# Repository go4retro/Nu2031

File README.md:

# Nu2031 

This adapter allows one to utilize a Commodore 1541 disk drive as both a serial disk drive for the serial IEC-based Commodore computers (VIC-20, C64, +4, C16, C128, etc.) and also an IEEE-488 drive for the PET/CBM line of computer systems.

## Introduction

Nu2031 ("New" 2031, with new in quotes because it's not really new :-)) comprises a two part hardware modification for the Commodore 1541 disk drive.  The first part is a 6522 Versatile Interface Adapter (VIA) daughterboard that dynamically switches specific VIA signals between the existing 1541 serial IEC port and an on-board IEEE-488 interface. The second part is a special multi-bank ROM-el replacement ROM that contains both the original 1541 DOS and a patched DOS that will enable the 1541 drive to function as a IEEE-488 CBM 2031 workalike drive. Using a single switch, connected to both adapter boards, the system can be quickly switched from one interface to the other.

This design is a refinement of many previous conversion projects, listed below:

The original (and largest, in my opinion) effort was included in an old 64'er magazine article.  Andre Fachat, who built the original interface, re-created the schematic and re-typed in the DOS patching utility, which are available at  http://www.6502.org/users/andre/cbmhw/ieee488/index.html. 

Dirk Wouters improved on the design by allowing the conversion to be "switched off", allowing continued use of the 1541 as a 1541 drive while supporting the IEEE-488 functionality.  Though his plans are no longer available, the project is discussed at https://www.lemon64.com/forum/viewtopic.php?t=71124 and at https://www.forum64.de/index.php?thread/91569-1541-to-ieee488-trimod-adapter/ (German).

Nu2031 was started before Dirk's project was presented, so it does not borrow from that design, though the two projects share a common set of functionality.

## Technical Details

The heart of the unit is the main adapter PCB (the ROM board is just a simple multi-bank ROM). The PCB contains both the 75160 and 75161 IEEE-488 interface ICs, as well as a Xilinx XC9572XL Complex Programmable Logic Device (CPLD).  Unlike the initial 64'er/Andre Fachat project, which simply wired the VIC to the interface ICs, or Dirk Wouter's interface, which uses banks of quad bilateral CMOS 4066 bilateral switches to connect or disconnect the various VIA signals to the 1541 motherboard or the IEEE 488 bus transceivers, this design implements the various IEEE-488 signal directions, as noted on page 2 of the 75161B datasheet (https://www.ti.com/lit/gpn/sn75161b). For reference, DC is always 'H' (5V), so the truth table can be somewhat simplified. The  ROM select signal noth only chooses which ROM bank to use, but is also used by the design to select which interface to enable.  The deselected interface is configured to allow other devices to continue to function on the de-selected bus.

If the system sees the ROM select signal change state, the interface immediately reconfigures the interface connects and resets the drive so the correct ROM will be initialized.

## Future Directions:

- Support method to "softswitch" the interface from one bus to another.

## License
Copyright (C) 2019-20  RETRO Innovations

These files are free designs; you can redistribute them and/or modify
them under the terms of the Creative Commons Attribution-ShareAlike 
4.0 International License.

You should have received a copy of the license along with this
work. If not, see <http://creativecommons.org/licenses/by-sa/4.0/>.

These files are distributed in the hope that they will be useful,
but WITHOUT ANY WARRANTY; without even the implied warranty of
MERCHANTABILITY or FITNESS FOR A PARTICULAR PURPOSE.  See the
license for more details.

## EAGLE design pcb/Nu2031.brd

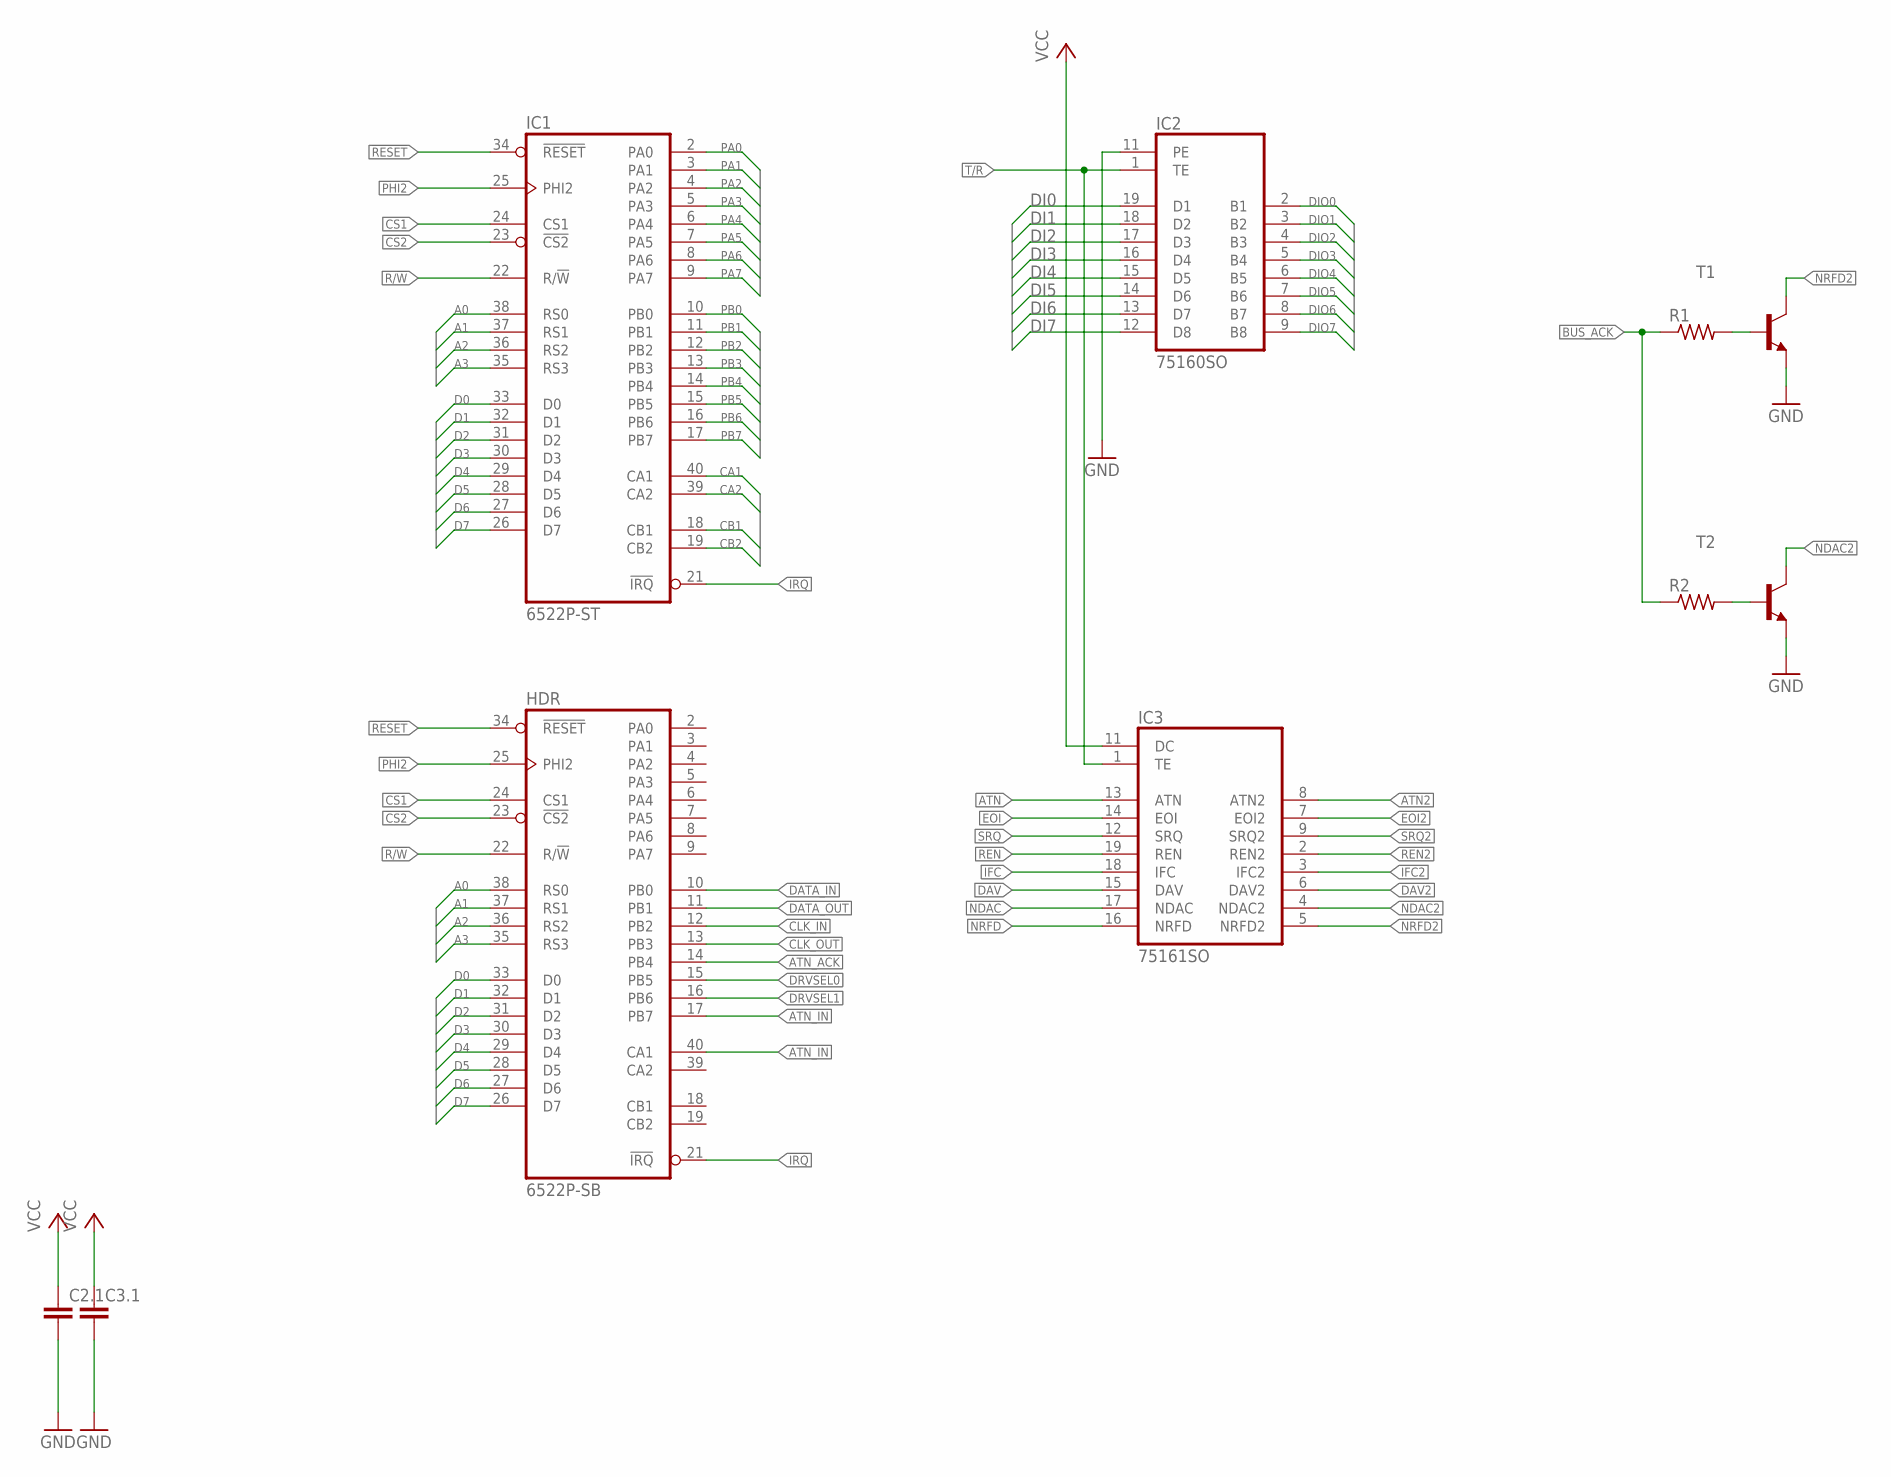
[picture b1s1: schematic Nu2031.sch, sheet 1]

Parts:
C2.1, C3.1: C-EUC0402; C0402
HDR: 6522P-SB; DIL40-SMD-REVERSE
IC1: 6522P-ST; DIL40-SMD
IC2: 75160SO; SO20L
IC3: 75161SO; SO20L
R1, R2: R-US_R0402; R0402
T1, T2: MMBT3904LT1-NPN-SOT23-BEC; SOT23-BEC

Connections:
!CS2: HDR.23 (!CS2), IC1.23 (!CS2)
!IRQ: HDR.21 (!IRQ), IC1.21 (!IRQ)
!RESET: HDR.34 (!RESET), IC1.34 (!RESET); also elsewhere on the board
A0: HDR.38 (RS0), IC1.38 (RS0)
A1: HDR.37 (RS1), IC1.37 (RS1)
A2: HDR.36 (RS2), IC1.36 (RS2)
A3: HDR.35 (RS3), IC1.35 (RS3)
ATN: IC3.13 (ATN); also elsewhere on the board
ATN2: IC3.8 (ATN2); also elsewhere on the board
ATN_ACK: HDR.14 (PB4); also elsewhere on the board
ATN_IN: HDR.17 (PB7), HDR.40 (CA1); also elsewhere on the board
BUS_ACK: R1.1, R2.1; also elsewhere on the board
CA1: IC1.40 (CA1); also elsewhere on the board
CA2: IC1.39 (CA2); also elsewhere on the board
CB1: IC1.18 (CB1); also elsewhere on the board
CB2: IC1.19 (CB2); also elsewhere on the board
CLK_IN: HDR.12 (PB2); also elsewhere on the board
CLK_OUT: HDR.13 (PB3); also elsewhere on the board
CS1: HDR.24 (CS1), IC1.24 (CS1)
D0: HDR.33 (D0), IC1.33 (D0)
D1: HDR.32 (D1), IC1.32 (D1)
D2: HDR.31 (D2), IC1.31 (D2)
D3: HDR.30 (D3), IC1.30 (D3)
D4: HDR.29 (D4), IC1.29 (D4)
D5: HDR.28 (D5), IC1.28 (D5)
D6: HDR.27 (D6), IC1.27 (D6)
D7: HDR.26 (D7), IC1.26 (D7)
DATA_IN: HDR.10 (PB0); also elsewhere on the board
DATA_OUT: HDR.11 (PB1); also elsewhere on the board
DAV: IC3.15 (DAV); also elsewhere on the board
DAV2: IC3.6 (DAV2); also elsewhere on the board
DI0: IC2.19 (D1); also elsewhere on the board
DI1: IC2.18 (D2); also elsewhere on the board
DI2: IC2.17 (D3); also elsewhere on the board
DI3: IC2.16 (D4); also elsewhere on the board
DI4: IC2.15 (D5); also elsewhere on the board
DI5: IC2.14 (D6); also elsewhere on the board
DI6: IC2.13 (D7); also elsewhere on the board
DI7: IC2.12 (D8); also elsewhere on the board
DIO0: IC2.2 (B1); also elsewhere on the board
DIO1: IC2.3 (B2); also elsewhere on the board
DIO2: IC2.4 (B3); also elsewhere on the board
DIO3: IC2.5 (B4); also elsewhere on the board
DIO4: IC2.6 (B5); also elsewhere on the board
DIO5: IC2.7 (B6); also elsewhere on the board
DIO6: IC2.8 (B7); also elsewhere on the board
DIO7: IC2.9 (B8); also elsewhere on the board
DRVSEL0: HDR.15 (PB5); also elsewhere on the board
DRVSEL1: HDR.16 (PB6); also elsewhere on the board
EOI: IC3.14 (EOI); also elsewhere on the board
EOI2: IC3.7 (EOI2); also elsewhere on the board
GND: C2.1.2, C3.1.2, HDR.1 (GND), IC1.1 (GND), IC2.10 (GND), IC2.11 (PE), IC3.10 (GND), T1.E, T2.E; also elsewhere on the board
IFC: IC3.18 (IFC); also elsewhere on the board
IFC2: IC3.3 (IFC2); also elsewhere on the board
unnamed: R1.2, T1.B
unnamed: R2.2, T2.B
NDAC: IC3.17 (NDAC); also elsewhere on the board
NDAC2: IC3.4 (NDAC2), T2.C; also elsewhere on the board
NRFD: IC3.16 (NRFD); also elsewhere on the board
NRFD2: IC3.5 (NRFD2), T1.C; also elsewhere on the board
PA0: IC1.2 (PA0); also elsewhere on the board
PA1: IC1.3 (PA1); also elsewhere on the board
PA2: IC1.4 (PA2); also elsewhere on the board
PA3: IC1.5 (PA3); also elsewhere on the board
PA4: IC1.6 (PA4); also elsewhere on the board
PA5: IC1.7 (PA5); also elsewhere on the board
PA6: IC1.8 (PA6); also elsewhere on the board
PA7: IC1.9 (PA7); also elsewhere on the board
PB0: IC1.10 (PB0); also elsewhere on the board
PB1: IC1.11 (PB1); also elsewhere on the board
PB2: IC1.12 (PB2); also elsewhere on the board
PB3: IC1.13 (PB3); also elsewhere on the board
PB4: IC1.14 (PB4); also elsewhere on the board
PB5: IC1.15 (PB5); also elsewhere on the board
PB6: IC1.16 (PB6); also elsewhere on the board
PB7: IC1.17 (PB7); also elsewhere on the board
PHI2: HDR.25 (PHI2), IC1.25 (PHI2)
R/!W: HDR.22 (R/!W), IC1.22 (R/!W)
REN: IC3.19 (REN); also elsewhere on the board
REN2: IC3.2 (REN2); also elsewhere on the board
SRQ: IC3.12 (SRQ); also elsewhere on the board
SRQ2: IC3.9 (SRQ2); also elsewhere on the board
T/!R: IC2.1 (TE), IC3.1 (TE); also elsewhere on the board
VCC: C2.1.1, C3.1.1, HDR.20 (VCC), IC1.20 (VCC), IC2.20 (VCC), IC3.11 (DC), IC3.20 (VCC); also elsewhere on the board

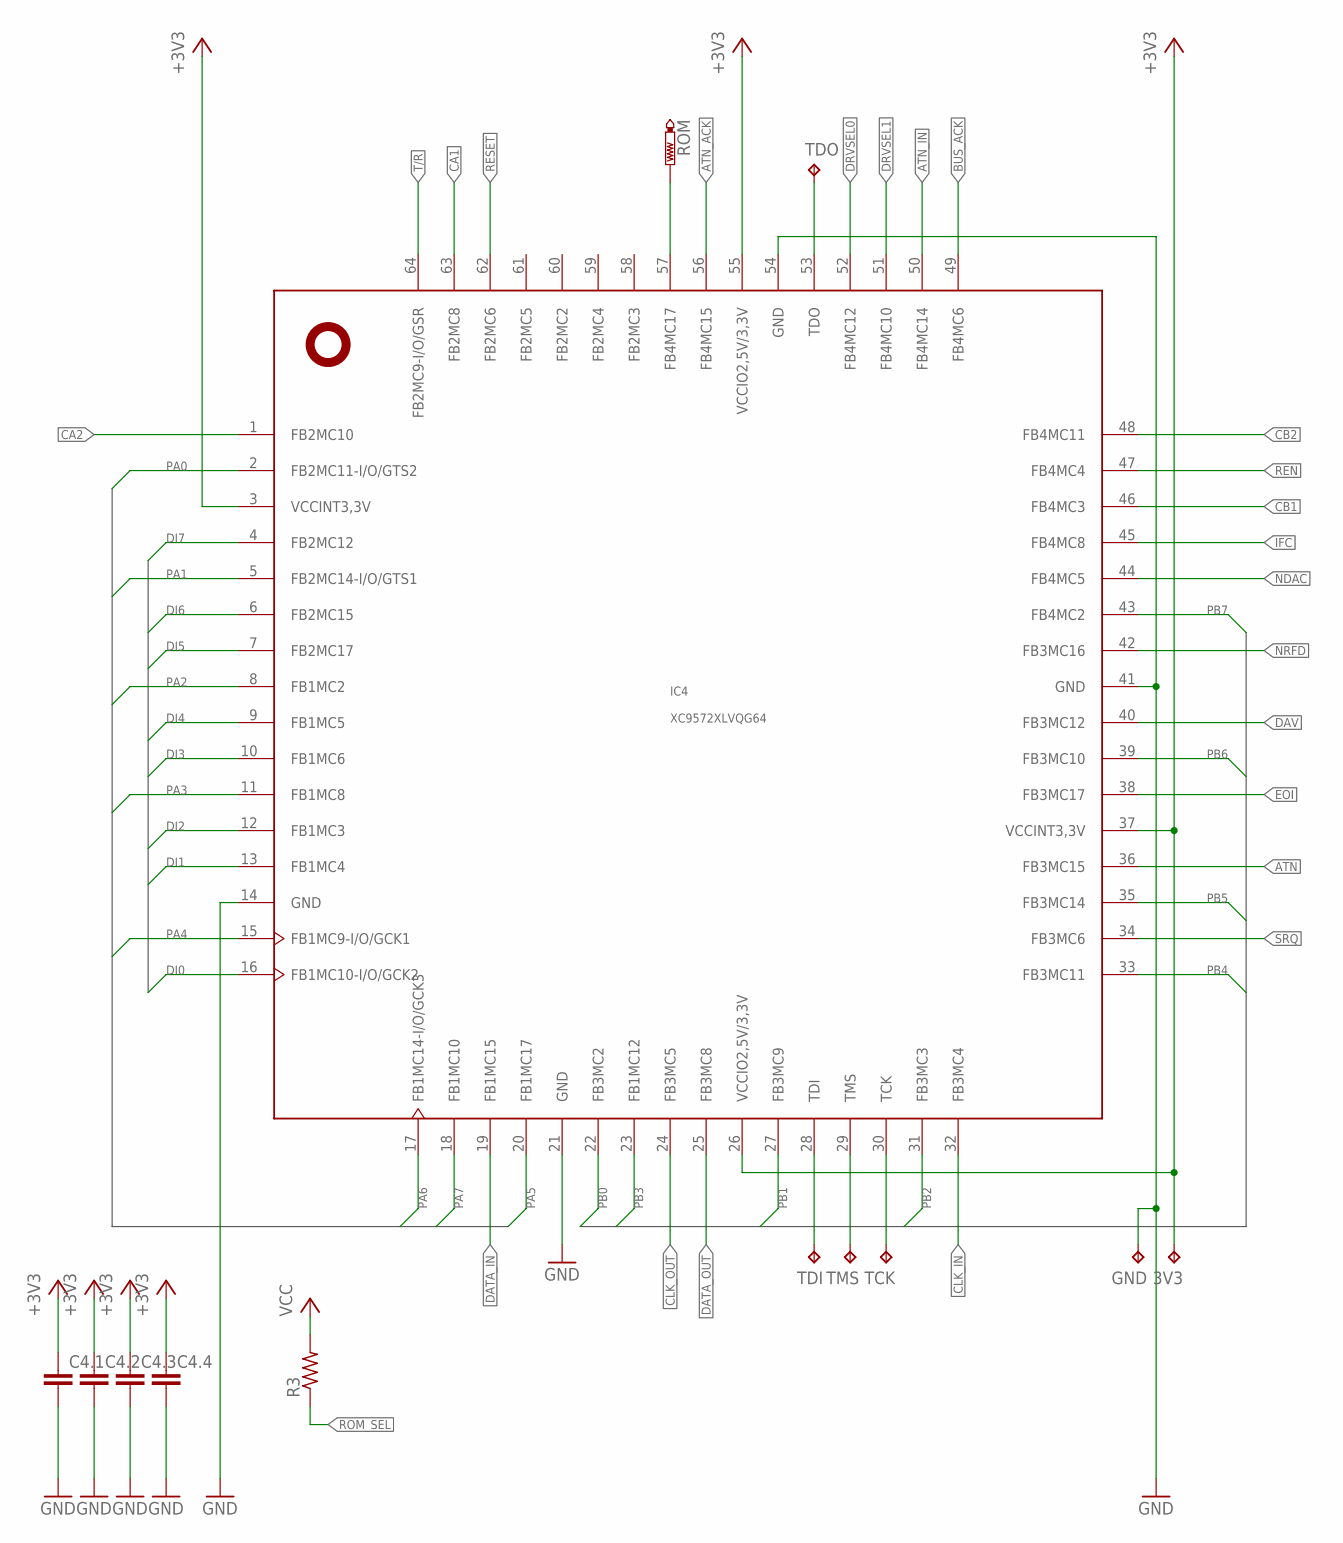
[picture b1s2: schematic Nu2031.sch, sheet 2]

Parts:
3V3: TPTP10R; TP10R
C4.1, C4.2, C4.3, C4.4: C-EUC0402; C0402
GND: TPTP10R; TP10R
IC4: XC9572XLVQG64; VQFP64
R3: R-US_R0402; R0402
ROM: PTR1B1,27; B1,27
TCK: TPTP10R; TP10R
TDI: TPTP10R; TP10R
TDO: TPTP10R; TP10R
TMS: TPTP10R; TP10R

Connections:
!RESET: IC4.62 (FB2MC6); also elsewhere on the board
+3V3: 3V3.TP, C4.1.1, C4.2.1, C4.3.1, C4.4.1, IC4.3 (VCCINT3,3V), IC4.26 (VCCIO2,5V/3,3V), IC4.37 (VCCINT3,3V), IC4.55 (VCCIO2,5V/3,3V); also elsewhere on the board
ATN: IC4.36 (FB3MC15); also elsewhere on the board
ATN_ACK: IC4.56 (FB4MC15); also elsewhere on the board
ATN_IN: IC4.50 (FB4MC14); also elsewhere on the board
BUS_ACK: IC4.49 (FB4MC6); also elsewhere on the board
CA1: IC4.63 (FB2MC8); also elsewhere on the board
CA2: IC4.1 (FB2MC10); also elsewhere on the board
CB1: IC4.46 (FB4MC3); also elsewhere on the board
CB2: IC4.48 (FB4MC11); also elsewhere on the board
CLK_IN: IC4.32 (FB3MC4); also elsewhere on the board
CLK_OUT: IC4.24 (FB3MC5); also elsewhere on the board
DATA_IN: IC4.19 (FB1MC15); also elsewhere on the board
DATA_OUT: IC4.25 (FB3MC8); also elsewhere on the board
DAV: IC4.40 (FB3MC12); also elsewhere on the board
DI0: IC4.16 (FB1MC10-I/O/GCK2); also elsewhere on the board
DI1: IC4.13 (FB1MC4); also elsewhere on the board
DI2: IC4.12 (FB1MC3); also elsewhere on the board
DI3: IC4.10 (FB1MC6); also elsewhere on the board
DI4: IC4.9 (FB1MC5); also elsewhere on the board
DI5: IC4.7 (FB2MC17); also elsewhere on the board
DI6: IC4.6 (FB2MC15); also elsewhere on the board
DI7: IC4.4 (FB2MC12); also elsewhere on the board
DRVSEL0: IC4.52 (FB4MC12); also elsewhere on the board
DRVSEL1: IC4.51 (FB4MC10); also elsewhere on the board
EOI: IC4.38 (FB3MC17); also elsewhere on the board
GND: C4.1.2, C4.2.2, C4.3.2, C4.4.2, GND.TP, IC4.14 (GND), IC4.21 (GND), IC4.41 (GND), IC4.54 (GND); also elsewhere on the board
IFC: IC4.45 (FB4MC8); also elsewhere on the board
NDAC: IC4.44 (FB4MC5); also elsewhere on the board
NRFD: IC4.42 (FB3MC16); also elsewhere on the board
PA0: IC4.2 (FB2MC11-I/O/GTS2); also elsewhere on the board
PA1: IC4.5 (FB2MC14-I/O/GTS1); also elsewhere on the board
PA2: IC4.8 (FB1MC2); also elsewhere on the board
PA3: IC4.11 (FB1MC8); also elsewhere on the board
PA4: IC4.15 (FB1MC9-I/O/GCK1); also elsewhere on the board
PA5: IC4.20 (FB1MC17); also elsewhere on the board
PA6: IC4.17 (FB1MC14-I/O/GCK3); also elsewhere on the board
PA7: IC4.18 (FB1MC10); also elsewhere on the board
PB0: IC4.22 (FB3MC2); also elsewhere on the board
PB1: IC4.27 (FB3MC9); also elsewhere on the board
PB2: IC4.31 (FB3MC3); also elsewhere on the board
PB3: IC4.23 (FB1MC12); also elsewhere on the board
PB4: IC4.33 (FB3MC11); also elsewhere on the board
PB5: IC4.35 (FB3MC14); also elsewhere on the board
PB6: IC4.39 (FB3MC10); also elsewhere on the board
PB7: IC4.43 (FB4MC2); also elsewhere on the board
REN: IC4.47 (FB4MC4); also elsewhere on the board
ROM_SEL: IC4.57 (FB4MC17), R3.1, ROM.TP
SRQ: IC4.34 (FB3MC6); also elsewhere on the board
T/!R: IC4.64 (FB2MC9-I/O/GSR); also elsewhere on the board
TCK: IC4.30 (TCK), TCK.TP
TDI: IC4.28 (TDI), TDI.TP
TDO: IC4.53 (TDO), TDO.TP
TMS: IC4.29 (TMS), TMS.TP
VCC: R3.2; also elsewhere on the board

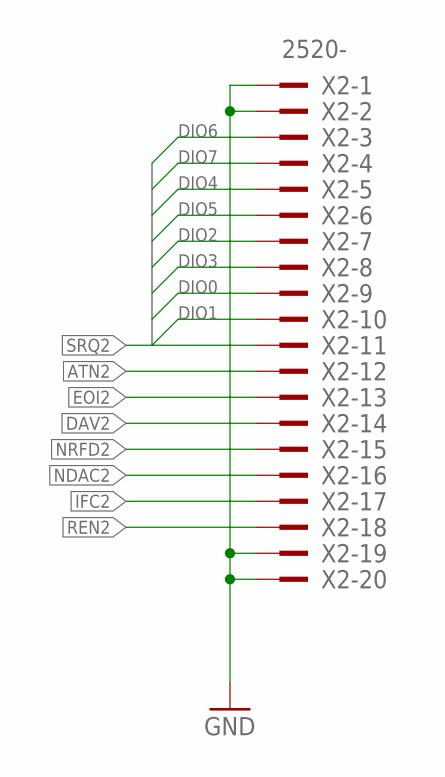
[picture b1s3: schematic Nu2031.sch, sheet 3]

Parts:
X2: 2520-; PAK100/2500-20

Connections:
ATN2: X2.12; also elsewhere on the board
DAV2: X2.14; also elsewhere on the board
DIO0: X2.9; also elsewhere on the board
DIO1: X2.10; also elsewhere on the board
DIO2: X2.7; also elsewhere on the board
DIO3: X2.8; also elsewhere on the board
DIO4: X2.5; also elsewhere on the board
DIO5: X2.6; also elsewhere on the board
DIO6: X2.3; also elsewhere on the board
DIO7: X2.4; also elsewhere on the board
EOI2: X2.13; also elsewhere on the board
GND: X2.1, X2.2, X2.19, X2.20; also elsewhere on the board
IFC2: X2.17; also elsewhere on the board
NDAC2: X2.16; also elsewhere on the board
NRFD2: X2.15; also elsewhere on the board
REN2: X2.18; also elsewhere on the board
SRQ2: X2.11; also elsewhere on the board

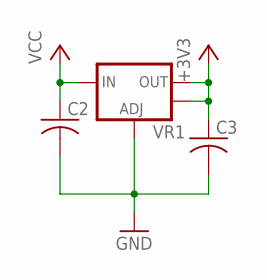
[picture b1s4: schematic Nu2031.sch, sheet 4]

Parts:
C2, C3: C-USC0805; C0805
VR1: V_REG_LM1117SOT223; SOT223

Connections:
+3V3: C3.1, VR1.2 (OUT), VR1.4 (OUT); also elsewhere on the board
GND: C2.2, C3.2, VR1.1 (ADJ); also elsewhere on the board
VCC: C2.1, VR1.3 (IN); also elsewhere on the board

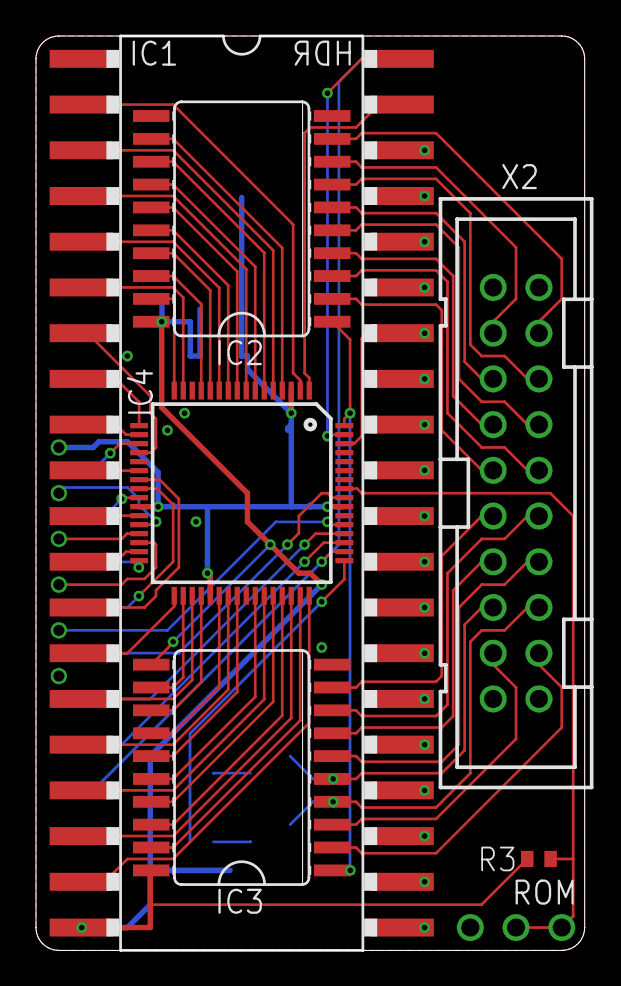
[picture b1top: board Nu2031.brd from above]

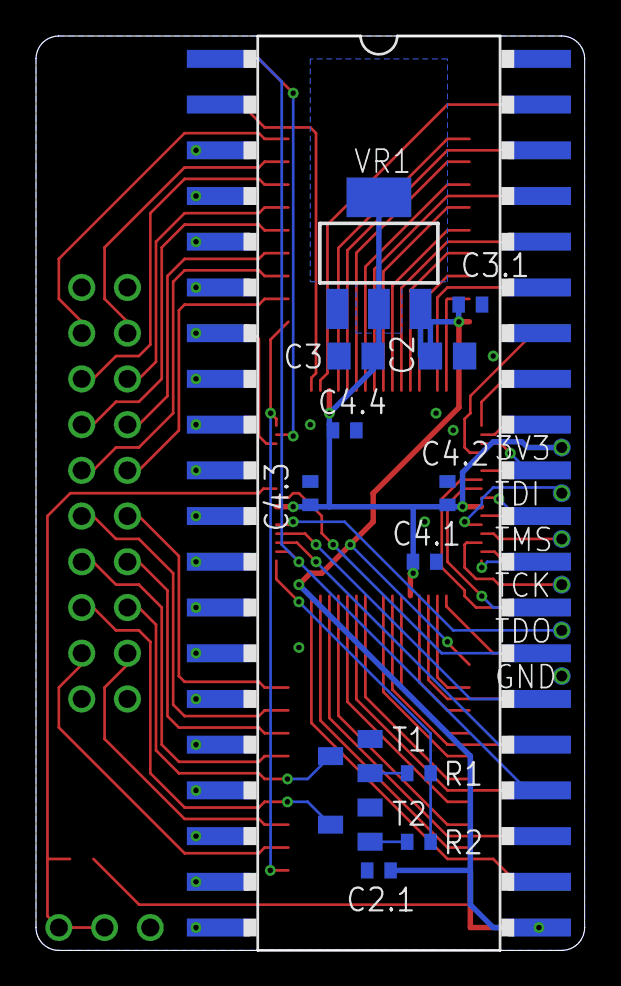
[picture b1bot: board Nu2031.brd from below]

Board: 2 copper layers, 30.5 x 50.8 mm, 27 parts (19 on the bottom side), 90 nets.

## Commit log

2018-08-04 Added schematic PNGs
2020-10-19 First working config
    * Fix some of the IEEE logic in HDL
    * Add resistor to ROM selection, to default to IEC
    * Add patched 1541 (2031-ish) DOS
2020-10-20 Implement auto-reset functionality and clean up Verilog a bit.

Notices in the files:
parts and their libraries:
SparkFun: Licensing: CC v3.0 Share-Alike You are welcome to use this library for commercial purposes.
